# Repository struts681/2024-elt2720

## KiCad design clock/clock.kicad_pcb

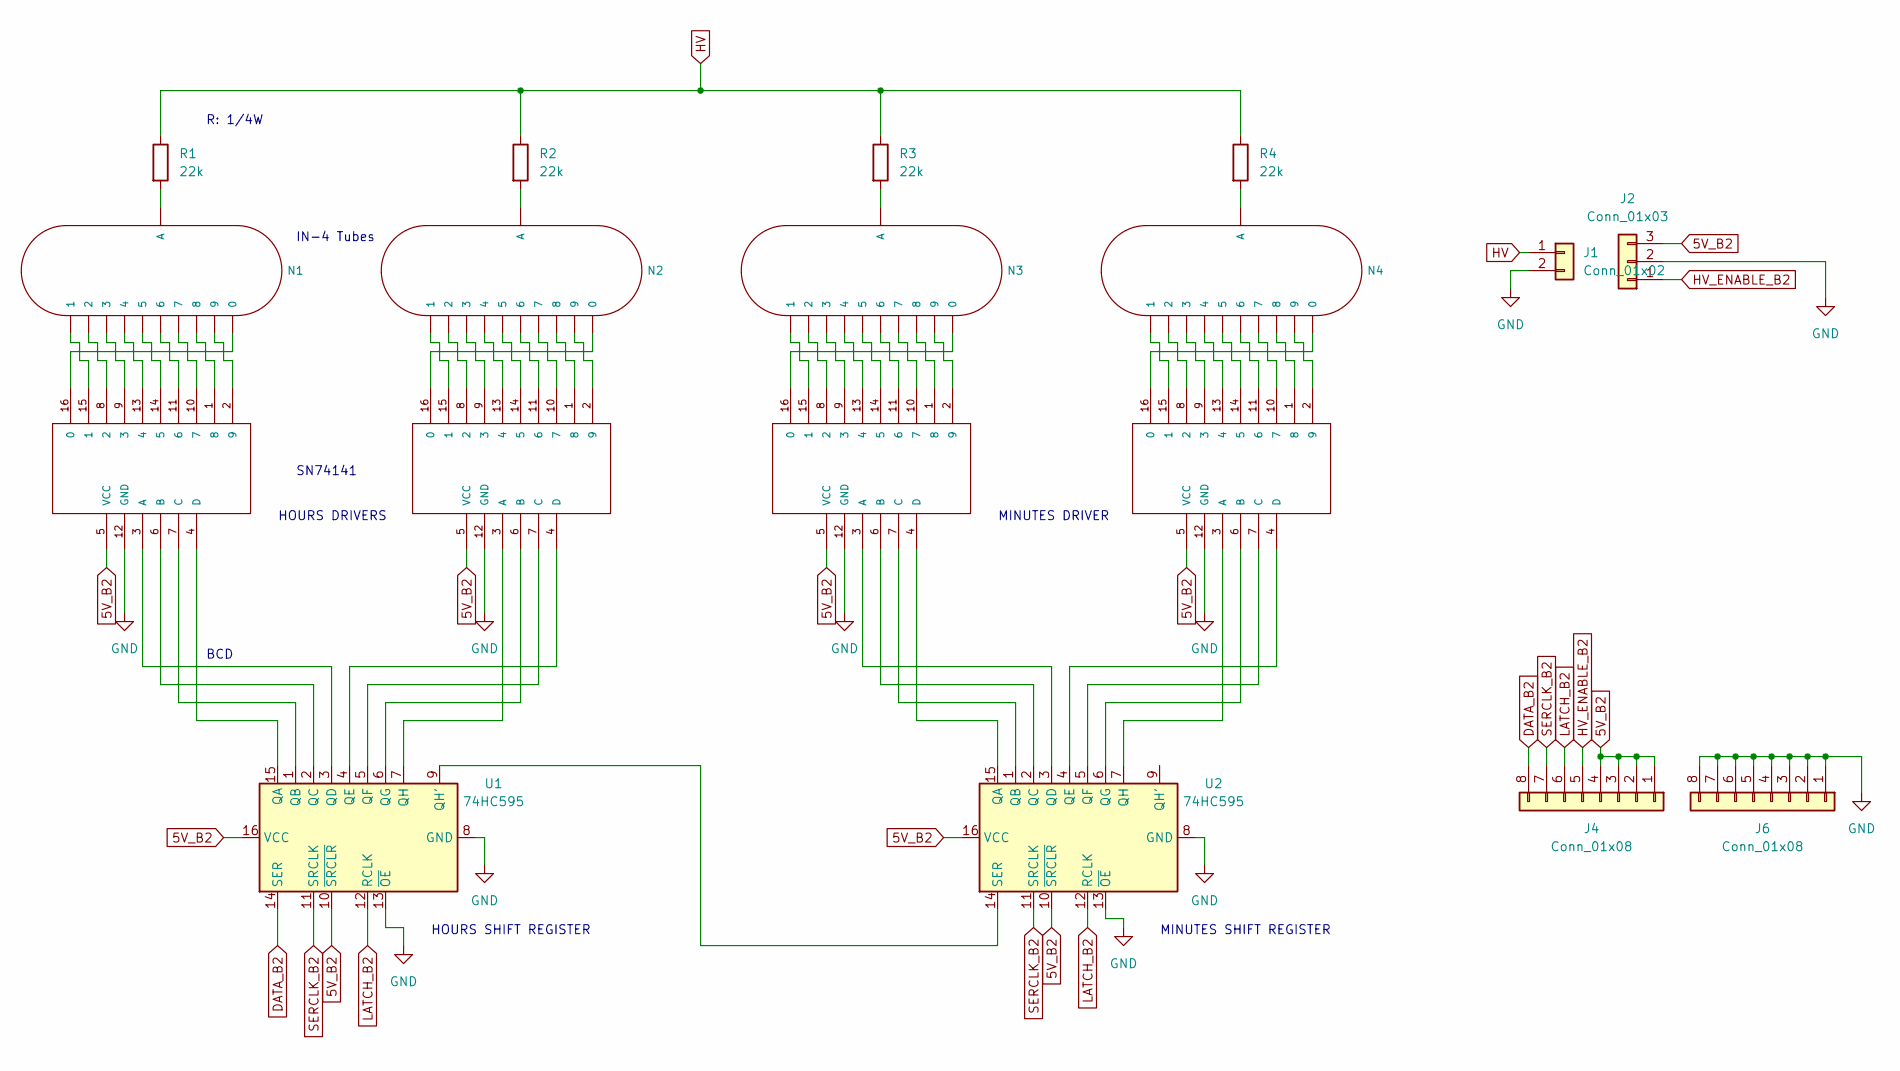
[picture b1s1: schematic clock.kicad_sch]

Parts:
J1: Conn_01x02; PinHeader_1x02_P2.54mm_Vertical
J2: Conn_01x03; PinHeader_1x03_P2.54mm_Vertical
J4, J6: Conn_01x08; PinHeader_1x08_P2.54mm_Vertical
M1, M2, M3, M4: 74141DIP16; nixiemisc-DIP16
N1, N2, N3, N4: IN-4; nixies-us-IN-4-DSUB
R1, R2, R3, R4: 22k; R_Axial_DIN0207_L6.3mm_D2.5mm_P7.62mm_Horizontal
U1, U2: 74HC595; DIP-16_W7.62mm

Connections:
5V_B2: J2.3, J4.1, J4.2, J4.3, J4.4, M1.5 (VCC), M2.5 (VCC), M3.5 (VCC), M4.5 (VCC), U1.10 (~SRCLR), U1.16 (VCC), U2.10 (~SRCLR), U2.16 (VCC)
DATA_B2: J4.8, U1.14 (SER)
GND: J1.2, J2.2, J6.1, J6.2, J6.3, J6.4, J6.5, J6.6, J6.7, J6.8, M1.12 (GND), M2.12 (GND), M3.12 (GND), M4.12 (GND), U1.8 (GND), U1.13 (~OE), U2.8 (GND), U2.13 (~OE)
HV: J1.1, R1.1, R2.1, R3.1, R4.1
HV_ENABLE_B2: J2.1, J4.5
LATCH_B2: J4.6, U1.12 (RCLK), U2.12 (RCLK)
unnamed: M1.16 (0), N1.0
unnamed: M1.15 (1), N1.1
unnamed: M1.8 (2), N1.2
unnamed: M1.9 (3), N1.3
unnamed: M1.13 (4), N1.4
unnamed: M1.14 (5), N1.5
unnamed: M1.11 (6), N1.6
unnamed: M1.10 (7), N1.7
unnamed: M1.1 (8), N1.8
unnamed: M1.2 (9), N1.9
unnamed: M1.3 (A), U1.3 (QD)
unnamed: M1.6 (B), U1.2 (QC)
unnamed: M1.7 (C), U1.1 (QB)
unnamed: M1.4 (D), U1.15 (QA)
unnamed: M2.16 (0), N2.0
unnamed: M2.15 (1), N2.1
unnamed: M2.8 (2), N2.2
unnamed: M2.9 (3), N2.3
unnamed: M2.13 (4), N2.4
unnamed: M2.14 (5), N2.5
unnamed: M2.11 (6), N2.6
unnamed: M2.10 (7), N2.7
unnamed: M2.1 (8), N2.8
unnamed: M2.2 (9), N2.9
unnamed: M2.3 (A), U1.7 (QH)
unnamed: M2.6 (B), U1.6 (QG)
unnamed: M2.7 (C), U1.5 (QF)
unnamed: M2.4 (D), U1.4 (QE)
unnamed: M3.16 (0), N3.0
unnamed: M3.15 (1), N3.1
unnamed: M3.8 (2), N3.2
unnamed: M3.9 (3), N3.3
unnamed: M3.13 (4), N3.4
unnamed: M3.14 (5), N3.5
unnamed: M3.11 (6), N3.6
unnamed: M3.10 (7), N3.7
unnamed: M3.1 (8), N3.8
unnamed: M3.2 (9), N3.9
unnamed: M3.3 (A), U2.3 (QD)
unnamed: M3.6 (B), U2.2 (QC)
unnamed: M3.7 (C), U2.1 (QB)
unnamed: M3.4 (D), U2.15 (QA)
unnamed: M4.16 (0), N4.0
unnamed: M4.15 (1), N4.1
unnamed: M4.8 (2), N4.2
unnamed: M4.9 (3), N4.3
unnamed: M4.13 (4), N4.4
unnamed: M4.14 (5), N4.5
unnamed: M4.11 (6), N4.6
unnamed: M4.10 (7), N4.7
unnamed: M4.1 (8), N4.8
unnamed: M4.2 (9), N4.9
unnamed: M4.3 (A), U2.7 (QH)
unnamed: M4.6 (B), U2.6 (QG)
unnamed: M4.7 (C), U2.5 (QF)
unnamed: M4.4 (D), U2.4 (QE)
unnamed: N1.A3 (A), R1.2
unnamed: N2.A3 (A), R2.2
unnamed: N3.A3 (A), R3.2
unnamed: N4.A3 (A), R4.2
unnamed: U1.9 (QH'), U2.14 (SER)
SERCLK_B2: J4.7, U1.11 (SRCLK), U2.11 (SRCLK)

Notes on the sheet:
HOURS DRIVERS
MINUTES DRIVER
IN-4 Tubes
R: 1/4W
BCD
HOURS SHIFT REGISTER
SN74141
MINUTES SHIFT REGISTER

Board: 2 copper layers, 18 parts (0 on the bottom side), 68 nets, no tracks yet.

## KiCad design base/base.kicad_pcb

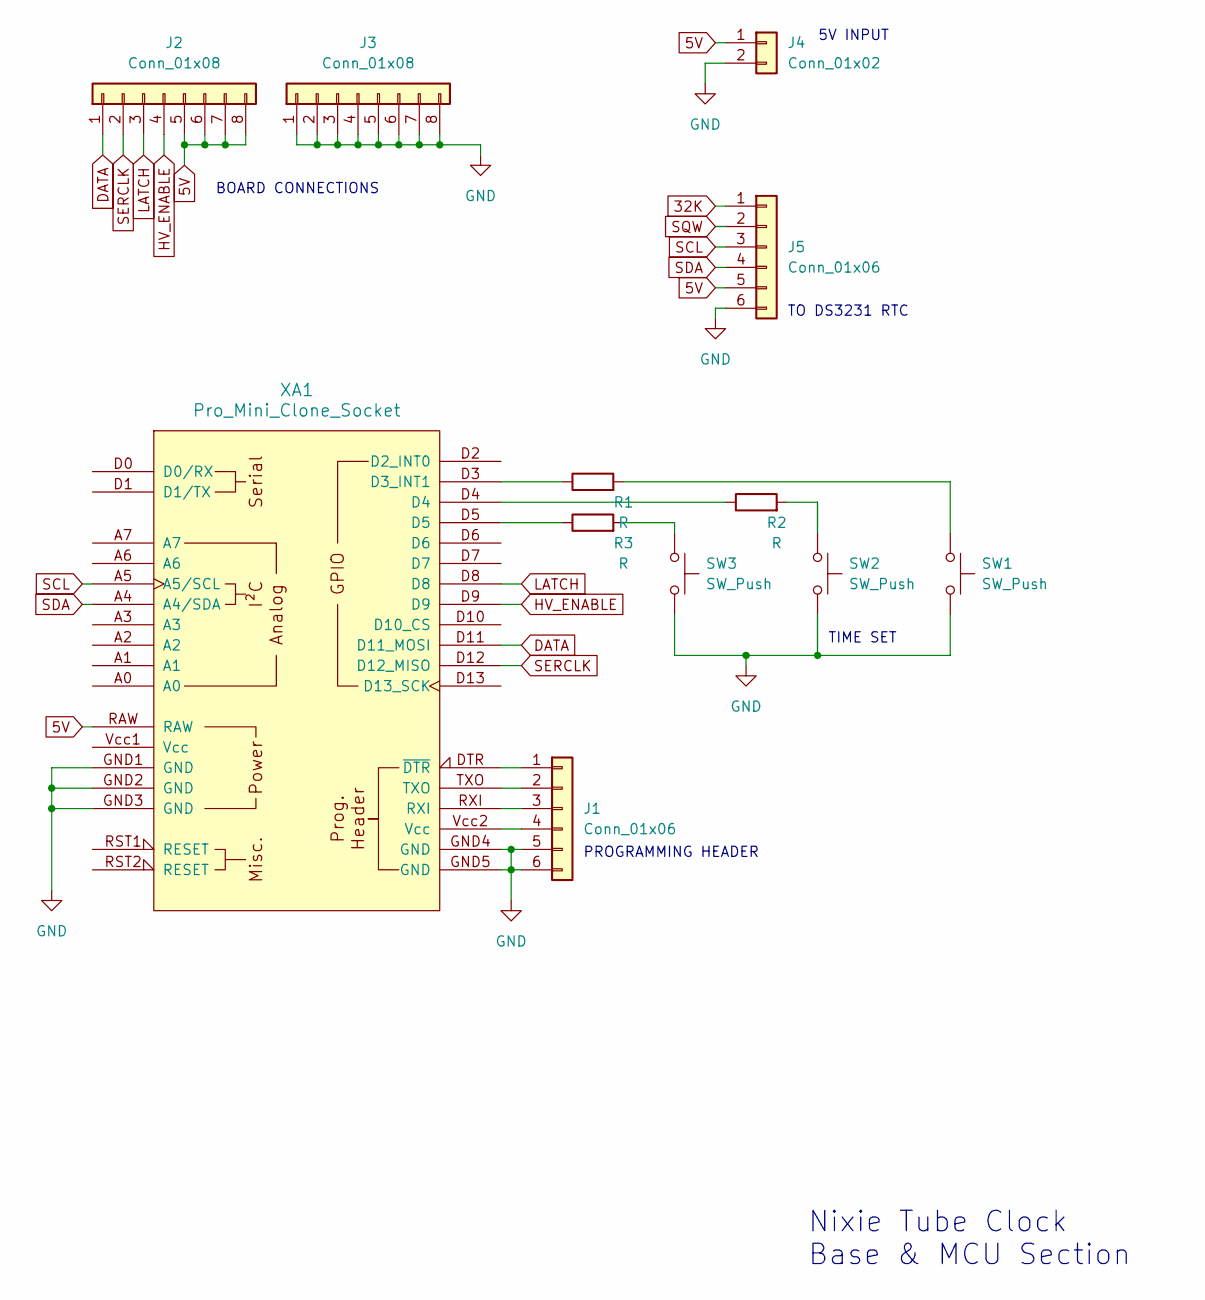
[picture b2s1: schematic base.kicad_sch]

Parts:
J1, J5: Conn_01x06; PinHeader_1x06_P2.54mm_Vertical
J2, J3: Conn_01x08; PinHeader_1x08_P2.54mm_Vertical
J4: Conn_01x02; PinHeader_1x02_P2.54mm_Vertical
R1, R2, R3: R; R_Axial_DIN0207_L6.3mm_D2.5mm_P7.62mm_Horizontal
SW1, SW2, SW3: SW_Push; PinHeader_1x02_P2.54mm_Vertical
XA1: Pro_Mini_Clone_Socket

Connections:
5V: J2.5, J2.6, J2.7, J2.8, J4.1, J5.5, XA1.RAW
32K: J5.1
DATA: J2.1, XA1.D11 (D11_MOSI)
GND: J1.5, J1.6, J3.1, J3.2, J3.3, J3.4, J3.5, J3.6, J3.7, J3.8, J4.2, J5.6, SW1.2, SW2.2, SW3.2, XA1.GND1 (GND), XA1.GND2 (GND), XA1.GND3 (GND), XA1.GND4 (GND), XA1.GND5 (GND)
HV_ENABLE: J2.4, XA1.D9
LATCH: J2.3, XA1.D8
unnamed: J1.1, XA1.DTR (~DTR)
unnamed: J1.2, XA1.TXO
unnamed: J1.3, XA1.RXI
unnamed: J1.4, XA1.Vcc2 (Vcc)
unnamed: R1.2, SW1.1
unnamed: R2.1, XA1.D4
unnamed: R2.2, SW2.1
unnamed: R3.1, XA1.D5
unnamed: R3.2, SW3.1
unnamed: R1.1, XA1.D3 (D3_INT1)
SCL: J5.3, XA1.A5 (A5/SCL)
SDA: J5.4, XA1.A4 (A4/SDA)
SERCLK: J2.2, XA1.D12 (D12_MISO)
SQW: J5.2

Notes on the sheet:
TO DS3231 RTC
5V INPUT
Nixie Tube Clock Base & MCU Section
PROGRAMMING HEADER
TIME SET
BOARD CONNECTIONS

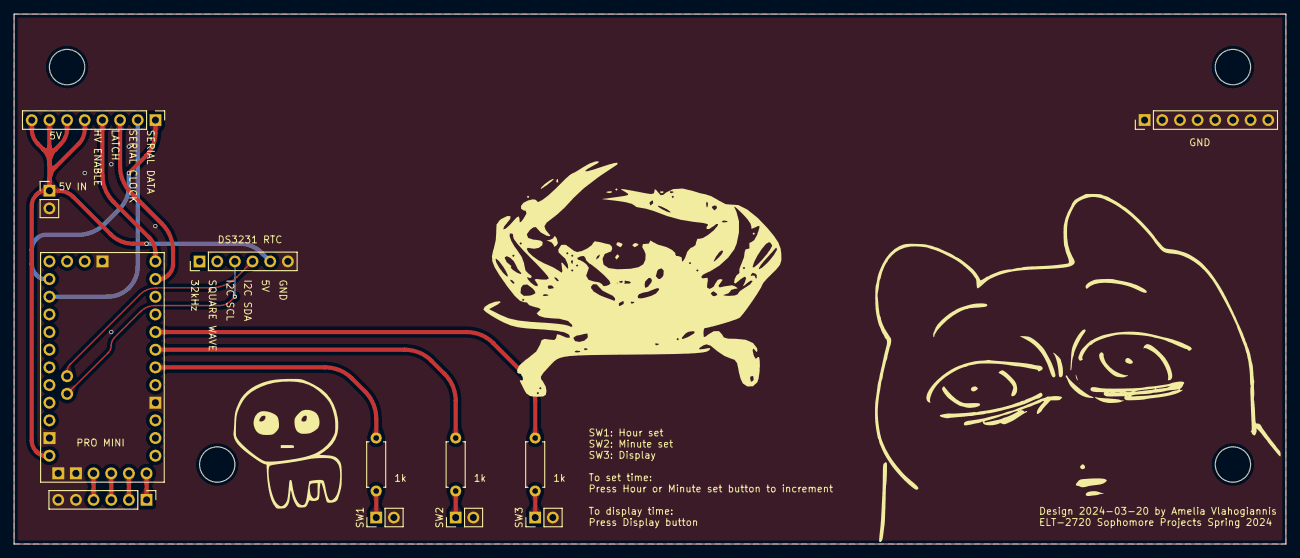
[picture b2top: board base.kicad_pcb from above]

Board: 2 copper layers, 182.9 x 76.2 mm, 12 parts (0 on the bottom side), 18 nets.

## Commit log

2024-05-14 upload
